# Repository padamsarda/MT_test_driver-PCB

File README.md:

# Magnetorquer Test PCB

## Overview
This PCB is designed to test different magnetorquer coils under varying operating conditions like voltage, current, and temperature.

The board uses an INA219 for current sensing and ADC voltage dividers for voltage measurement. 
It also has I²C and CAN headers so external sensors like magnetometers and temperature sensors can be connected if needed.

## Features
- DRV8871 motor driver
- INA219 current sensing
- ADC voltage measurement using voltage dividers
- USB Type-C interface
- SWD programming/debugging header
- I²C expansion header
- CAN header

## Applications
- Testing different magnetorquer coils
- Characterizing coil performance under different conditions
- Connecting external sensors for additional measurements
- Closed loop testing with magnetometers

## Notes
Designed and developed as part of **Team Anant**.

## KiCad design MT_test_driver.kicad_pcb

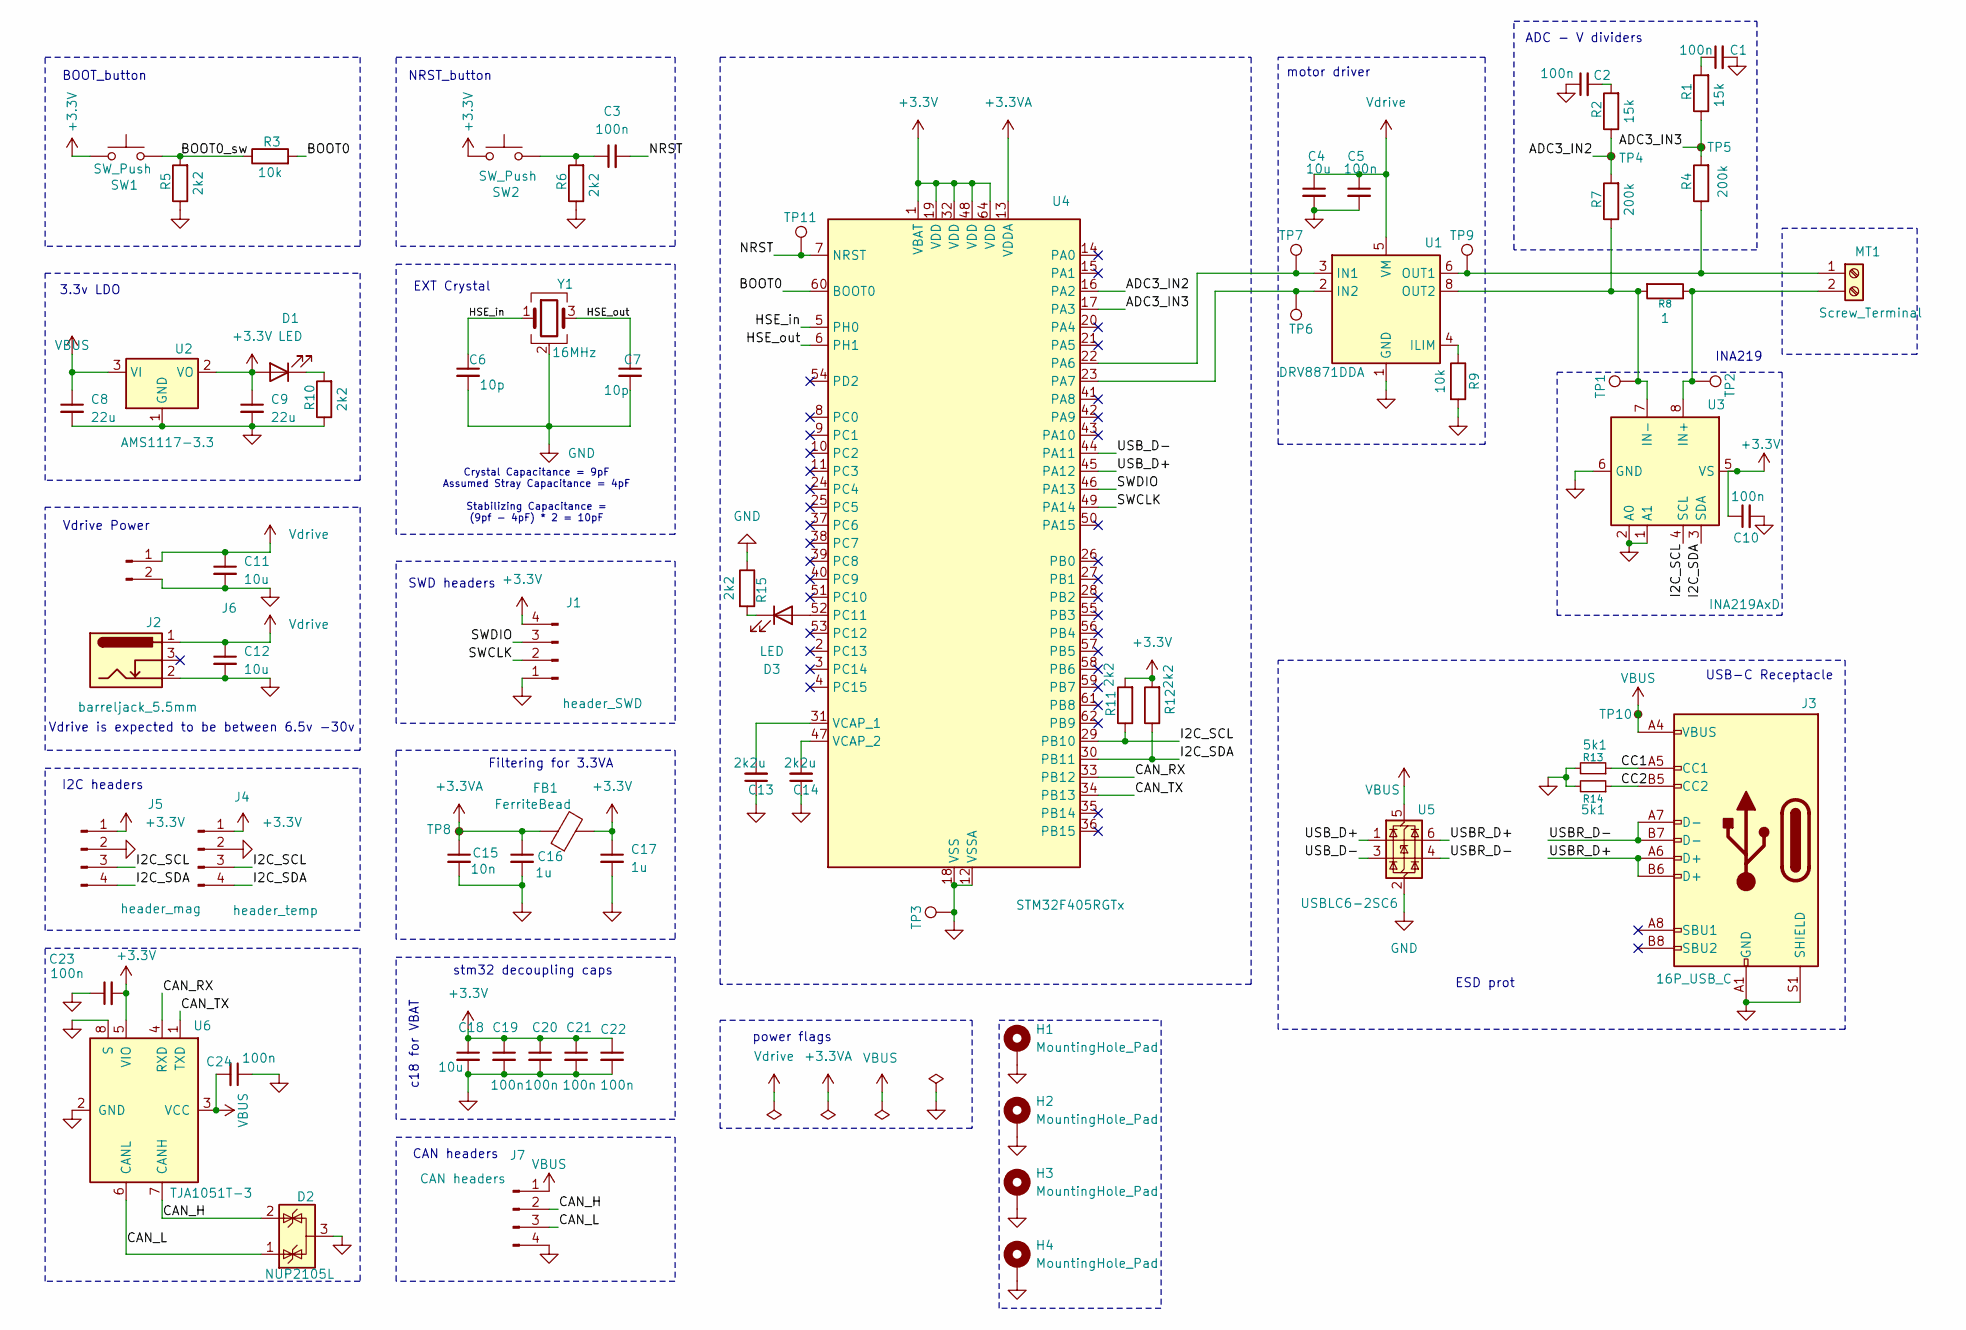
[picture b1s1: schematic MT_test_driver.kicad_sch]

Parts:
C1, C2, C3, C5, C10, C19, C20, C21, C22, C23, C24: 100n; C_0805_2012Metric_Pad1.18x1.45mm_HandSolder
C4, C11, C12, C18: 10u; C_0805_2012Metric_Pad1.18x1.45mm_HandSolder
C6, C7: 10p; C_0805_2012Metric_Pad1.18x1.45mm_HandSolder
C8, C9: 22u; C_0805_2012Metric_Pad1.18x1.45mm_HandSolder
C13, C14: 2k2u; C_0805_2012Metric_Pad1.18x1.45mm_HandSolder
C15: 10n; C_0805_2012Metric_Pad1.18x1.45mm_HandSolder
C16, C17: 1u; C_0805_2012Metric_Pad1.18x1.45mm_HandSolder
D1, D3: LED; LED_0805_2012Metric_Pad1.15x1.40mm_HandSolder
D2: NUP2105L; SOT-23
FB1: FerriteBead; L_0805_2012Metric_Pad1.05x1.20mm_HandSolder
H1, H2, H3, H4: MountingHole_Pad; MountingHole_2.2mm_M2_Pad
J1: header_SWD; PinHeader_1x04_P2.54mm_Vertical
J2: barreljack_5.5mm; BarrelJack_Horizontal
J3: 16P_USB_C; USB_C_Receptacle_G-Switch_GT-USB-7010ASV
J4: header_temp; PinHeader_1x04_P2.54mm_Vertical
J5: header_mag; PinHeader_1x04_P2.54mm_Vertical
J6: header_battery; PinHeader_1x02_P2.54mm_Vertical
J7: CAN headers; PinHeader_1x04_P2.54mm_Vertical
MT1: Screw_Terminal; TerminalBlock_Phoenix_MKDS-1,5-2-5.08_1x02_P5.08mm_Horizont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
R1, R2: 15k; R_0603_1608Metric_Pad0.98x0.95mm_HandSolder
R3, R9: 10k; R_0805_2012Metric_Pad1.20x1.40mm_HandSolder
R4, R7: 200k; R_0603_1608Metric_Pad0.98x0.95mm_HandSolder
R5, R6, R10, R11, R12, R15: 2k2; R_0805_2012Metric_Pad1.20x1.40mm_HandSolder
R8: 1; R_2512_6332Metric_Pad1.40x3.35mm_HandSolder
R13, R14: 5k1; R_0805_2012Metric_Pad1.20x1.40mm_HandSolder
SW1, SW2: SW_Push; tactile switch 4.5_4.5
TP1, TP2, TP3, TP6, TP7, TP9: TestPoint; PinHeader_1x01_P2.54mm_Vertical
TP4, TP5, TP8, TP10: TestPoint_Small; TestPoint_Pad_D1.5mm
TP11: TestPoint; TestPoint_Pad_D1.5mm
U1: DRV8871DDA; Texas_HTSOP-8-1EP_3.9x4.9mm_P1.27mm_EP2.95x4.9mm_Mask2.4x3.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
U2: AMS1117-3.3; SOT-223-3_TabPin2
U3: INA219AxD; SOIC-8_3.9x4.9mm_P1.27mm
U4: STM32F405RGTx; LQFP-64_10x10mm_P0.5mm
U5: USBLC6-2SC6; SOT-23-6
U6: TJA1051T-3; SOIC-8_3.9x4.9mm_P1.27mm
Y1: 16MHz; Crystal_SMD_3225-4Pin_3.2x2.5mm_HandSoldering

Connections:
+3.3V: C9.1, C10.1, C17.1, C18.1, C19.1, C20.1, C21.1, C22.1, C23.2, D1.2 (A), FB1.2, J1.4, J4.1, J5.1, R11.2, R12.2, SW1.1, SW2.1, U2.2 (VO), U3.5 (VS), U4.1 (VBAT), U4.19 (VDD), U4.32 (VDD), U4.48 (VDD), U4.64 (VDD), U6.5 (VIO)
+3.3VA: C15.1, C16.1, FB1.1, TP8.1, U4.13 (VDDA)
/ADC3_IN2: R2.1, R7.2, TP4.1, U4.16 (PA2)
/ADC3_IN3: R1.1, R4.2, TP5.1, U4.17 (PA3)
/BOOT0: R3.2, U4.60 (BOOT0)
/BOOT0_sw: R3.1, R5.2, SW1.2
/CAN_H: D2.2 (K), J7.2, U6.7 (CANH)
/CAN_L: D2.1 (K), J7.3, U6.6 (CANL)
/CAN_RX: U4.33 (PB12), U6.4 (RXD)
/CAN_TX: U4.34 (PB13), U6.1 (TXD)
/CC1: J3.A5 (CC1), R13.1
/CC2: J3.B5 (CC2), R14.1
/HSE_in: C6.1, U4.5 (PH0), Y1.1
/HSE_out: C7.1, U4.6 (PH1), Y1.3
/I2C_SCL: J4.3, J5.3, R11.1, U3.4 (SCL), U4.29 (PB10)
/I2C_SDA: J4.4, J5.4, R12.1, U3.3 (SDA), U4.30 (PB11)
/NRST: C3.2, TP11.1, U4.7 (NRST)
/SWCLK: J1.2, U4.49 (PA14)
/SWDIO: J1.3, U4.46 (PA13)
/USBR_D+: J3.A6 (D+), J3.B6 (D+), U5.6 (I/O1)
/USBR_D-: J3.A7 (D-), J3.B7 (D-), U5.4 (I/O2)
/USB_D+: U4.45 (PA12), U5.1 (I/O1)
/USB_D-: U4.44 (PA11), U5.3 (I/O2)
GND: C1.2, C2.1, C4.2, C5.2, C6.2, C7.2, C8.2, C9.2, C10.2, C11.2, C12.2, C13.1, C14.1, C15.2, C16.2, C17.2, C18.2, C19.2, C20.2, C21.2, C22.2, C23.1, C24.1, D2.3 (A), H1.1, H2.1, H3.1, H4.1, J1.1, J2.2, J3.A1 (GND), J3.A12 (GND), J3.B1 (GND), J3.B12 (GND), J3.S1 (SHIELD), J4.2, J5.2, J6.2, J7.4, R5.1, R6.1, R9.2, R10.1, R13.2, R14.2, R15.1, TP3.1, U1.1 (GND), U1.7 (GND), U1.9 (GND), U2.1 (GND), U3.1 (A1), U3.2 (A0), U3.6 (GND), U4.12 (VSSA), U4.18 (VSS), U4.63 (VSS), U5.2 (GND), U6.2 (GND), U6.8 (S), Y1.2 (G), Y1.4 (G)
unnamed: C1.1, R1.2
unnamed: C2.2, R2.2
unnamed: C3.1, R6.2, SW2.2
unnamed: D1.1 (K), R10.2
unnamed: D3.2 (A), U4.52 (PC11)
unnamed: D3.1 (K), R15.2
unnamed: MT1.1, R4.1, TP9.1, U1.6 (OUT1)
unnamed: MT1.2, R8.1, TP2.1, U3.8 (IN+)
unnamed: R9.1, U1.4 (ILIM)
unnamed: TP7.1, U1.3 (IN1), U4.22 (PA6)
unnamed: TP6.1, U1.2 (IN2), U4.23 (PA7)
unnamed: R7.1, R8.2, TP1.1, U1.8 (OUT2), U3.7 (IN-)
unnamed: C13.2, U4.31 (VCAP_1)
unnamed: C14.2, U4.47 (VCAP_2)
VBUS: C8.1, C24.2, J3.A4 (VBUS), J3.A9 (VBUS), J3.B4 (VBUS), J3.B9 (VBUS), J7.1, TP10.1, U2.3 (VI), U5.5 (VBUS), U6.3 (VCC)
Vdrive: C4.1, C5.1, C11.1, C12.1, J2.1, J6.1, U1.5 (VM)

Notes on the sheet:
EXT Crystal
SWD headers
Filtering for 3.3VA
NRST_button
motor driver
Vdrive is expected to be between 6.5v -30v
3.3v LDO
Vdrive Power
USB-C Receptacle
I2C headers
Crystal Capacitance = 9pF Assumed Stray Capacitance = 4pF Stabilizing Capacitance = (9pf - 4pF) * 2 = 10pF
ESD prot
CAN headers
BOOT_button
c18 for VBAT
power flags
stm32 decoupling caps
ADC - V dividers
INA219

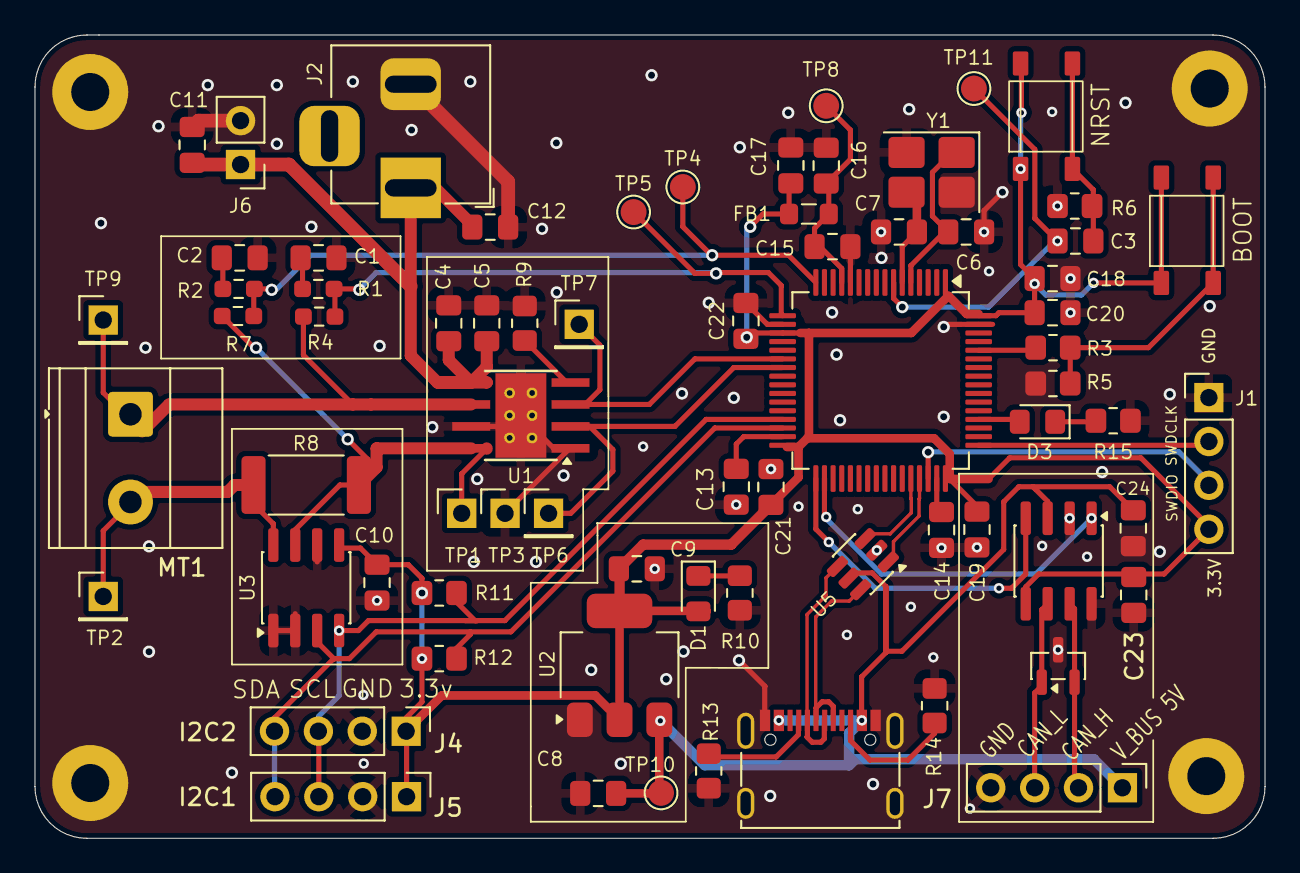
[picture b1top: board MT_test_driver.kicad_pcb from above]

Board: 2 copper layers, 71.2 x 46.5 mm, 75 parts (0 on the bottom side), 40 nets.

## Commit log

2026-06-14 minor changes
2026-06-16 pcb layout done, stm32 configuration changed etc
2026-06-16 Added CAN bus, other small changes
2026-06-17 changes in layout , moving components
2026-06-18 final changes
2026-06-18 added gpio LED for debugging
